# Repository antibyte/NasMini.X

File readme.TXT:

Single Chip Nascom 2 Emulator

Credits:
Z80 Emulation :         : Marat Fayzullin http://fms.komkon.org/EMUL8/
Video and PS/2 based on : Katsumi http://hp.vector.co.jp/authors/VA016157/
SD & FAT Filesystem     : Elm Chan, Aiden Morrison, Riccardo Leonardi

What's working :

z80 CPU
24K RAM (2K used by video buffer and NAS-SYS)
10K ROM (2K NAS-SYS 3 and 8K Microsoft Basic)
Loading NAS format files from SD card(press F1)
Saving RAM to NAS format on SD card (press F2)
Composite Video 48x16 video output, advanced graphics character ROM is included.
PS/2 keyboard with special keys:
  F1 - Load NAS file from SD card (works for BASIC)
  F2 - Save RAM (0x0100-0x7000) as NAS file to SD card (works for BASIC)
  Scroll lock - Trigger NMI
Single step emulation
RS232 is partialy working. Received Data is corrupted, maybe hardware
problem, as is used a Bluetooth adapter. 

ToDo :

Cassette Emulation (real or/and SD)
RS232 bootloader (if possible)
Map Z80PIO access to I2C Port expander, or remaining physical pins ?

Speed:
Maybe slower than the real thing, but really usable.

Thoughts:
A PIC32MX250 is used featuring USB, but there is not enought space left for any
USB stack.
But as the price difference to the non-USB MX150 is negligible for small
projects, it may be good to have it on board for possible reuse in future
projects.

First steps:
Visit http://www.nascomhomepage.com/
 
Type "J" after start to jump to Microsoft Basic
Most NAS files load to 0x01000. Type E1000 to run them

antibyte 11/2013

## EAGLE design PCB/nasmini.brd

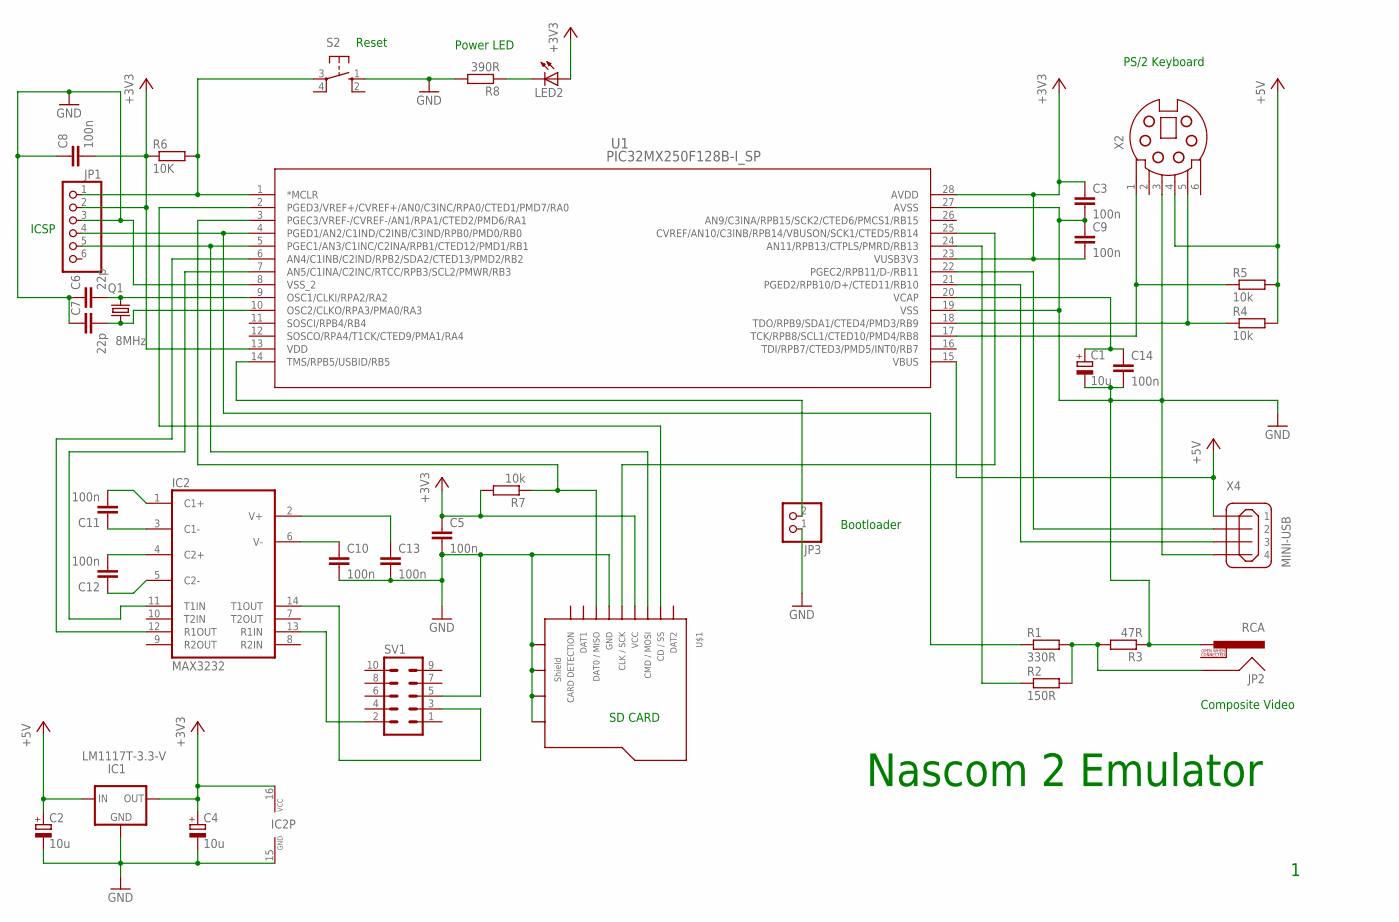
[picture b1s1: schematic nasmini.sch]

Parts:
C1, C2, C4: 10u; E2,5-5
C3, C5, C8, C9, C10, C11, C12, C13, C14: 100n; C025-025X050
C6, C7: 22p; C025-025X050
IC1: LM1117T-3.3-V; TO220V
IC2: MAX3232; DIL16
JP1: PINHD-1X6; 1X06
JP2: RCA
JP3: PINHD-1X2; 1X02
LED2: LED3MM
Q1: 8MHz; HC49/S
R1: 330R; 0207/7
R2: 150R; 0207/7
R3: 47R; 0207/7
R4, R5, R7: 10k; 0207/7
R6: 10K; 0207/7
R8: 390R; 0207/7
S2: 10-XX; B3F-10XX
SV1: MA05-2
U1: PIC32MX250F128B-I_SP; SPDIP28_300MC
U$1: MICROSD_CARD_POLLIN; MR**-AP*03**
X2: MDSSV-F06; SSV-BC06
X4: MINI-USB; 85-32006-201-1

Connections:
+3V3: C3.1, C4.+, C5.1, C8.2, C9.2, IC1.2 (OUT), IC2.16 (VCC), JP1.2, LED2.A, R6.1, R7.2, U1.13 (VDD), U1.23 (VUSB3V3), U1.28 (AVDD), U$1.VCC
+5V: C2.+, IC1.3 (IN), R4.2, R5.2, U1.15 (VBUS), X2.4, X4.1
GND: C1.-, C2.-, C3.2, C4.-, C5.2, C6.1, C7.1, C8.1, C9.1, C10.2, C13.2, C14.2, IC1.1 (GND), IC2.15 (GND), JP1.3, JP2.PIN, JP3.1, R3.1, R8.2, S2.1 (S), SV1.5, U1.8 (VSS_2), U1.19 (VSS), U1.27 (AVSS), U$1.GND, U$1.SHD_1 (SHD1), U$1.SHD_2 (SHD2), U$1.SHD_3 (SHD3), U$1.SHD_4 (SHD4), X2.3, X4.4
unnamed: R5.1, U1.17 (TCK/RPB8/SCL1/CTED10/PMD4/RB8), X2.1
unnamed: R4.1, U1.18 (TDO/RPB9/SDA1/CTED4/PMD3/RB9), X2.5
unnamed: R2.1, U1.24 (AN11/RPB13/CTPLS/PMRD/RB13)
unnamed: JP3.2, U1.14 (TMS/RPB5/USBID/RB5)
unnamed: JP2.SHELL, R1.2, R2.2, R3.2
unnamed: IC2.13 (R1IN), SV1.2
unnamed: C1.+, C14.1, U1.20 (VCAP)
unnamed: JP1.4, R1.1, U1.4 (PGED1/AN2/C1IND/C2INB/C3IND/RPB0/PMD0/R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)
unnamed: JP1.1, R6.2, S2.3, U1.1 (*MCLR)
unnamed: U1.25 (CVREF/AN10/C3INB/RPB14/VBUSON/SCK1/CTED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), U$1.CLK (CLK/SCK)
unnamed: U1.2 (PGED3/VREF+/CVREF+/AN0/C3INC/RPA0/CTED1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), U$1.DAT3/CS (CD/SS)
unnamed: R7.1, U1.3 (PGEC3/VREF-/CVREF-/AN1/RPA1/CTED2/PMD6/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), U$1.DAT0 (DAT0/MISO)
unnamed: JP1.5, U1.5 (PGEC1/AN3/C1INC/C2INA/RPB1/CTED12/PMD1/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), U$1.CMD (CMD/MOSI)
unnamed: U1.21 (PGED2/RPB10/D+/CTED11/RB10), X4.3
unnamed: C7.2, Q1.1, U1.10 (OSC2/CLKO/RPA3/PMA0/RA3)
unnamed: C6.2, Q1.2, U1.9 (OSC1/CLKI/RPA2/RA2)
unnamed: U1.22 (PGEC2/RPB11/D-/RB11), X4.2
unnamed: C13.1, IC2.2 (V+)
unnamed: C10.1, IC2.6 (V-)
unnamed: C12.1, IC2.5 (C2-)
unnamed: C12.2, IC2.4 (C2+)
unnamed: C11.1, IC2.3 (C1-)
unnamed: C11.2, IC2.1 (C1+)
unnamed: IC2.11 (T1IN), U1.7 (AN5/C1INA/C2INC/RTCC/RPB3/SCL2/PMWR/RB3)
unnamed: IC2.12 (R1OUT), U1.6 (AN4/C1INB/C2IND/RPB2/SDA2/CTED13/PMD2/R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)
unnamed: LED2.K (C), R8.1
unnamed: IC2.14 (T1OUT), SV1.3

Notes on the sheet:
Composite Video
PS/2 Keyboard
Nascom 2 Emulator
ICSP
SD CARD
Power LED
Reset
Bootloader

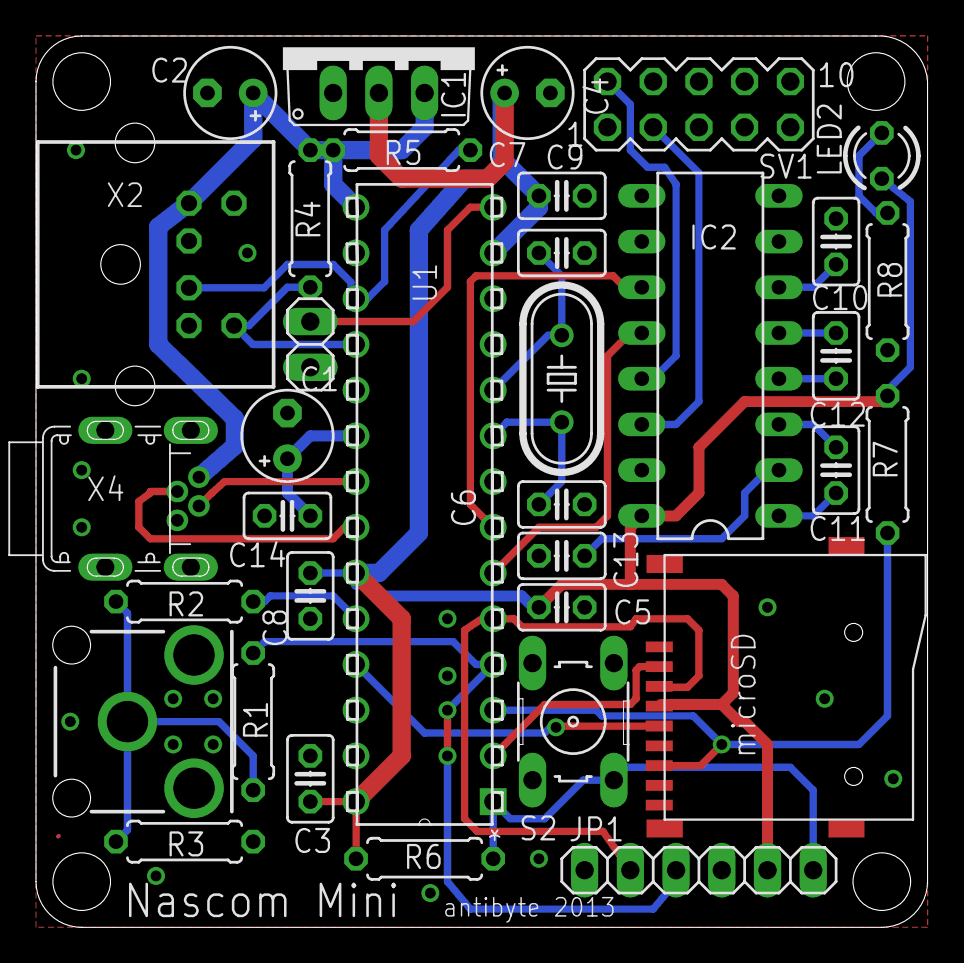
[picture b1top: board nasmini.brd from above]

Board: 2 copper layers, 49.5 x 49.5 mm, 35 parts (0 on the bottom side), 30 nets.

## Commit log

2013-11-23 Schematics and Eagle files

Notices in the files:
parts and their libraries:
SparkFun-Connectors: Licensing: CC v3.0 Share-Alike You are welcome to use this library for commercial purposes.
